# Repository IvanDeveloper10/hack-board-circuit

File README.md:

## HEARTH BOARD
This project is a PCB with a theme of heart, a design perfect and the circuit fine.

This project uses passive components, has an excellent LED layout, and is a gift for a colleague. I created the heart shape using the line drawing tool on the PCB cutouts.

I used a capacitor, a potentiometer, a push button, 11 LEDs and also a battery cell as a power source.

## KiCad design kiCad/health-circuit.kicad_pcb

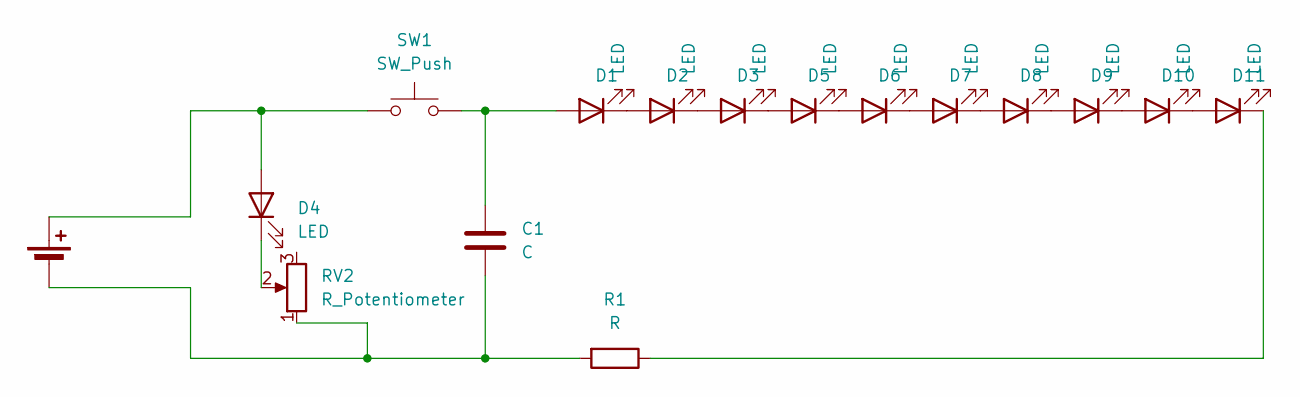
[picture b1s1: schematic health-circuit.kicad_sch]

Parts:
BT1: Battery_Cell; BatteryHolder_Keystone_3034_1x20mm
C1: C; CP_Radial_D8.0mm_P5.00mm
D1, D2, D3, D4, D5, D6, D7, D8, D9, D10, D11: LED; LED_D5.0mm
R1: R; R_Axial_DIN0207_L6.3mm_D2.5mm_P7.62mm_Horizontal
RV2: R_Potentiometer; Potentiometer_Vishay_T73YP_Vertical
SW1: SW_Push; SW_PUSH_6mm

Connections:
unnamed: BT1.1 (+), D4.2 (A), SW1.1
unnamed: BT1.2 (-), C1.2, R1.2, RV2.1
unnamed: C1.1, D1.2 (A), SW1.2
unnamed: D1.1 (K), D2.2 (A)
unnamed: D2.1 (K), D3.2 (A)
unnamed: D3.1 (K), D5.2 (A)
unnamed: D4.1 (K), RV2.2
unnamed: D5.1 (K), D6.2 (A)
unnamed: D6.1 (K), D7.2 (A)
unnamed: D7.1 (K), D8.2 (A)
unnamed: D8.1 (K), D9.2 (A)
unnamed: D9.1 (K), D10.2 (A)
unnamed: D10.1 (K), D11.2 (A)
unnamed: D11.1 (K), R1.1

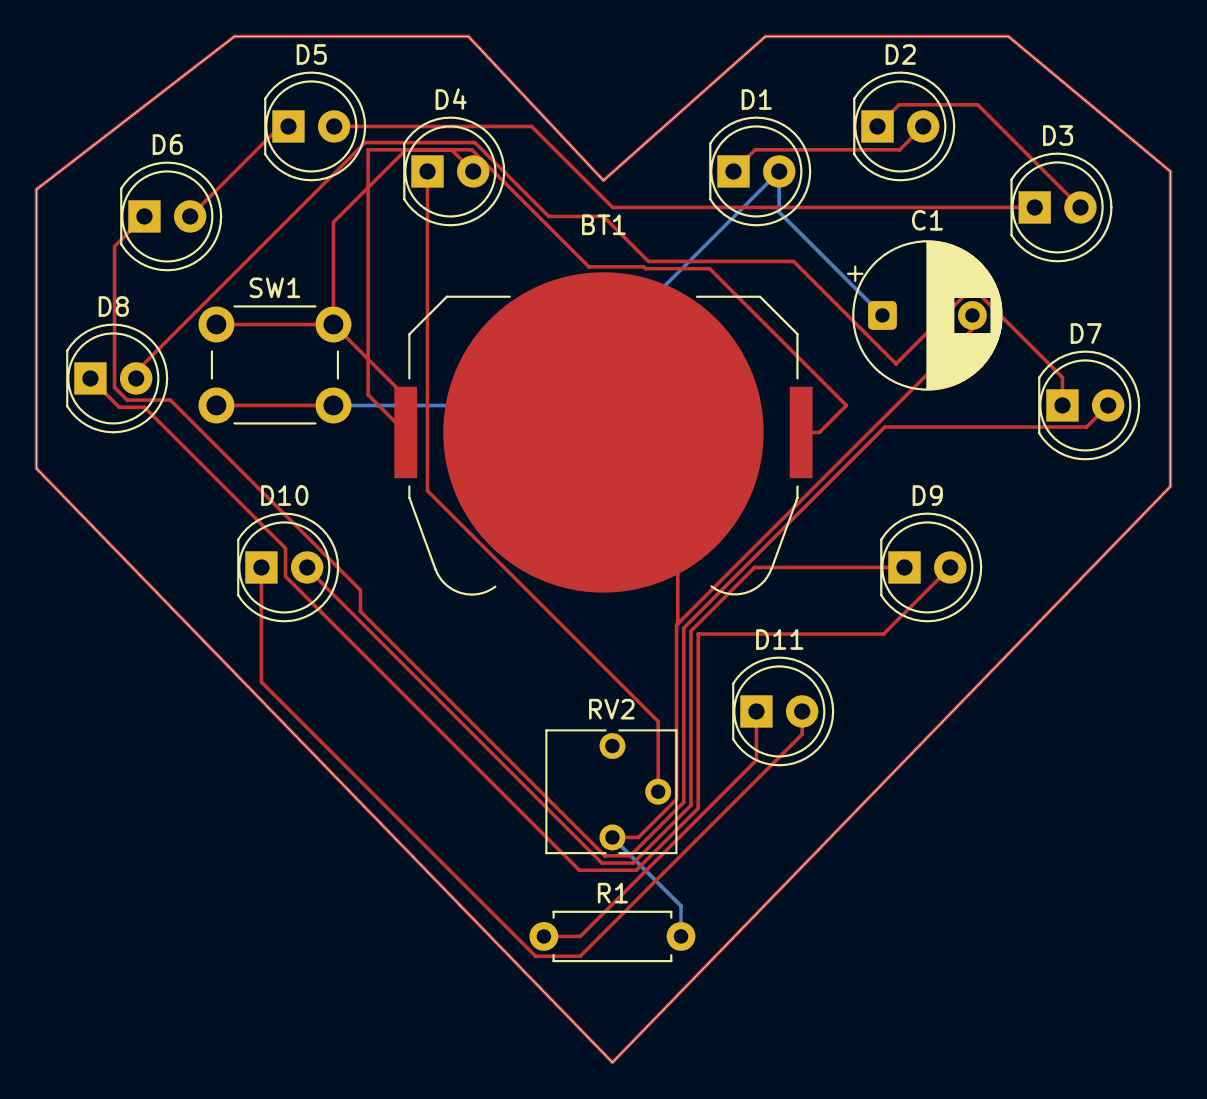
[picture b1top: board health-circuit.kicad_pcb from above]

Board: 2 copper layers, 63.0 x 57.0 mm, 16 parts (0 on the bottom side), 14 nets.

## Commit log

2025-11-30 Rename 'HACK BOARD' to 'HEALTH BOARD'
2025-11-30 Add Hello.txt with greeting message
2025-11-30 Fix title and enhance project description in README
    Updated project title and added detailed description with images.
2025-11-30 Update README with project details and images
